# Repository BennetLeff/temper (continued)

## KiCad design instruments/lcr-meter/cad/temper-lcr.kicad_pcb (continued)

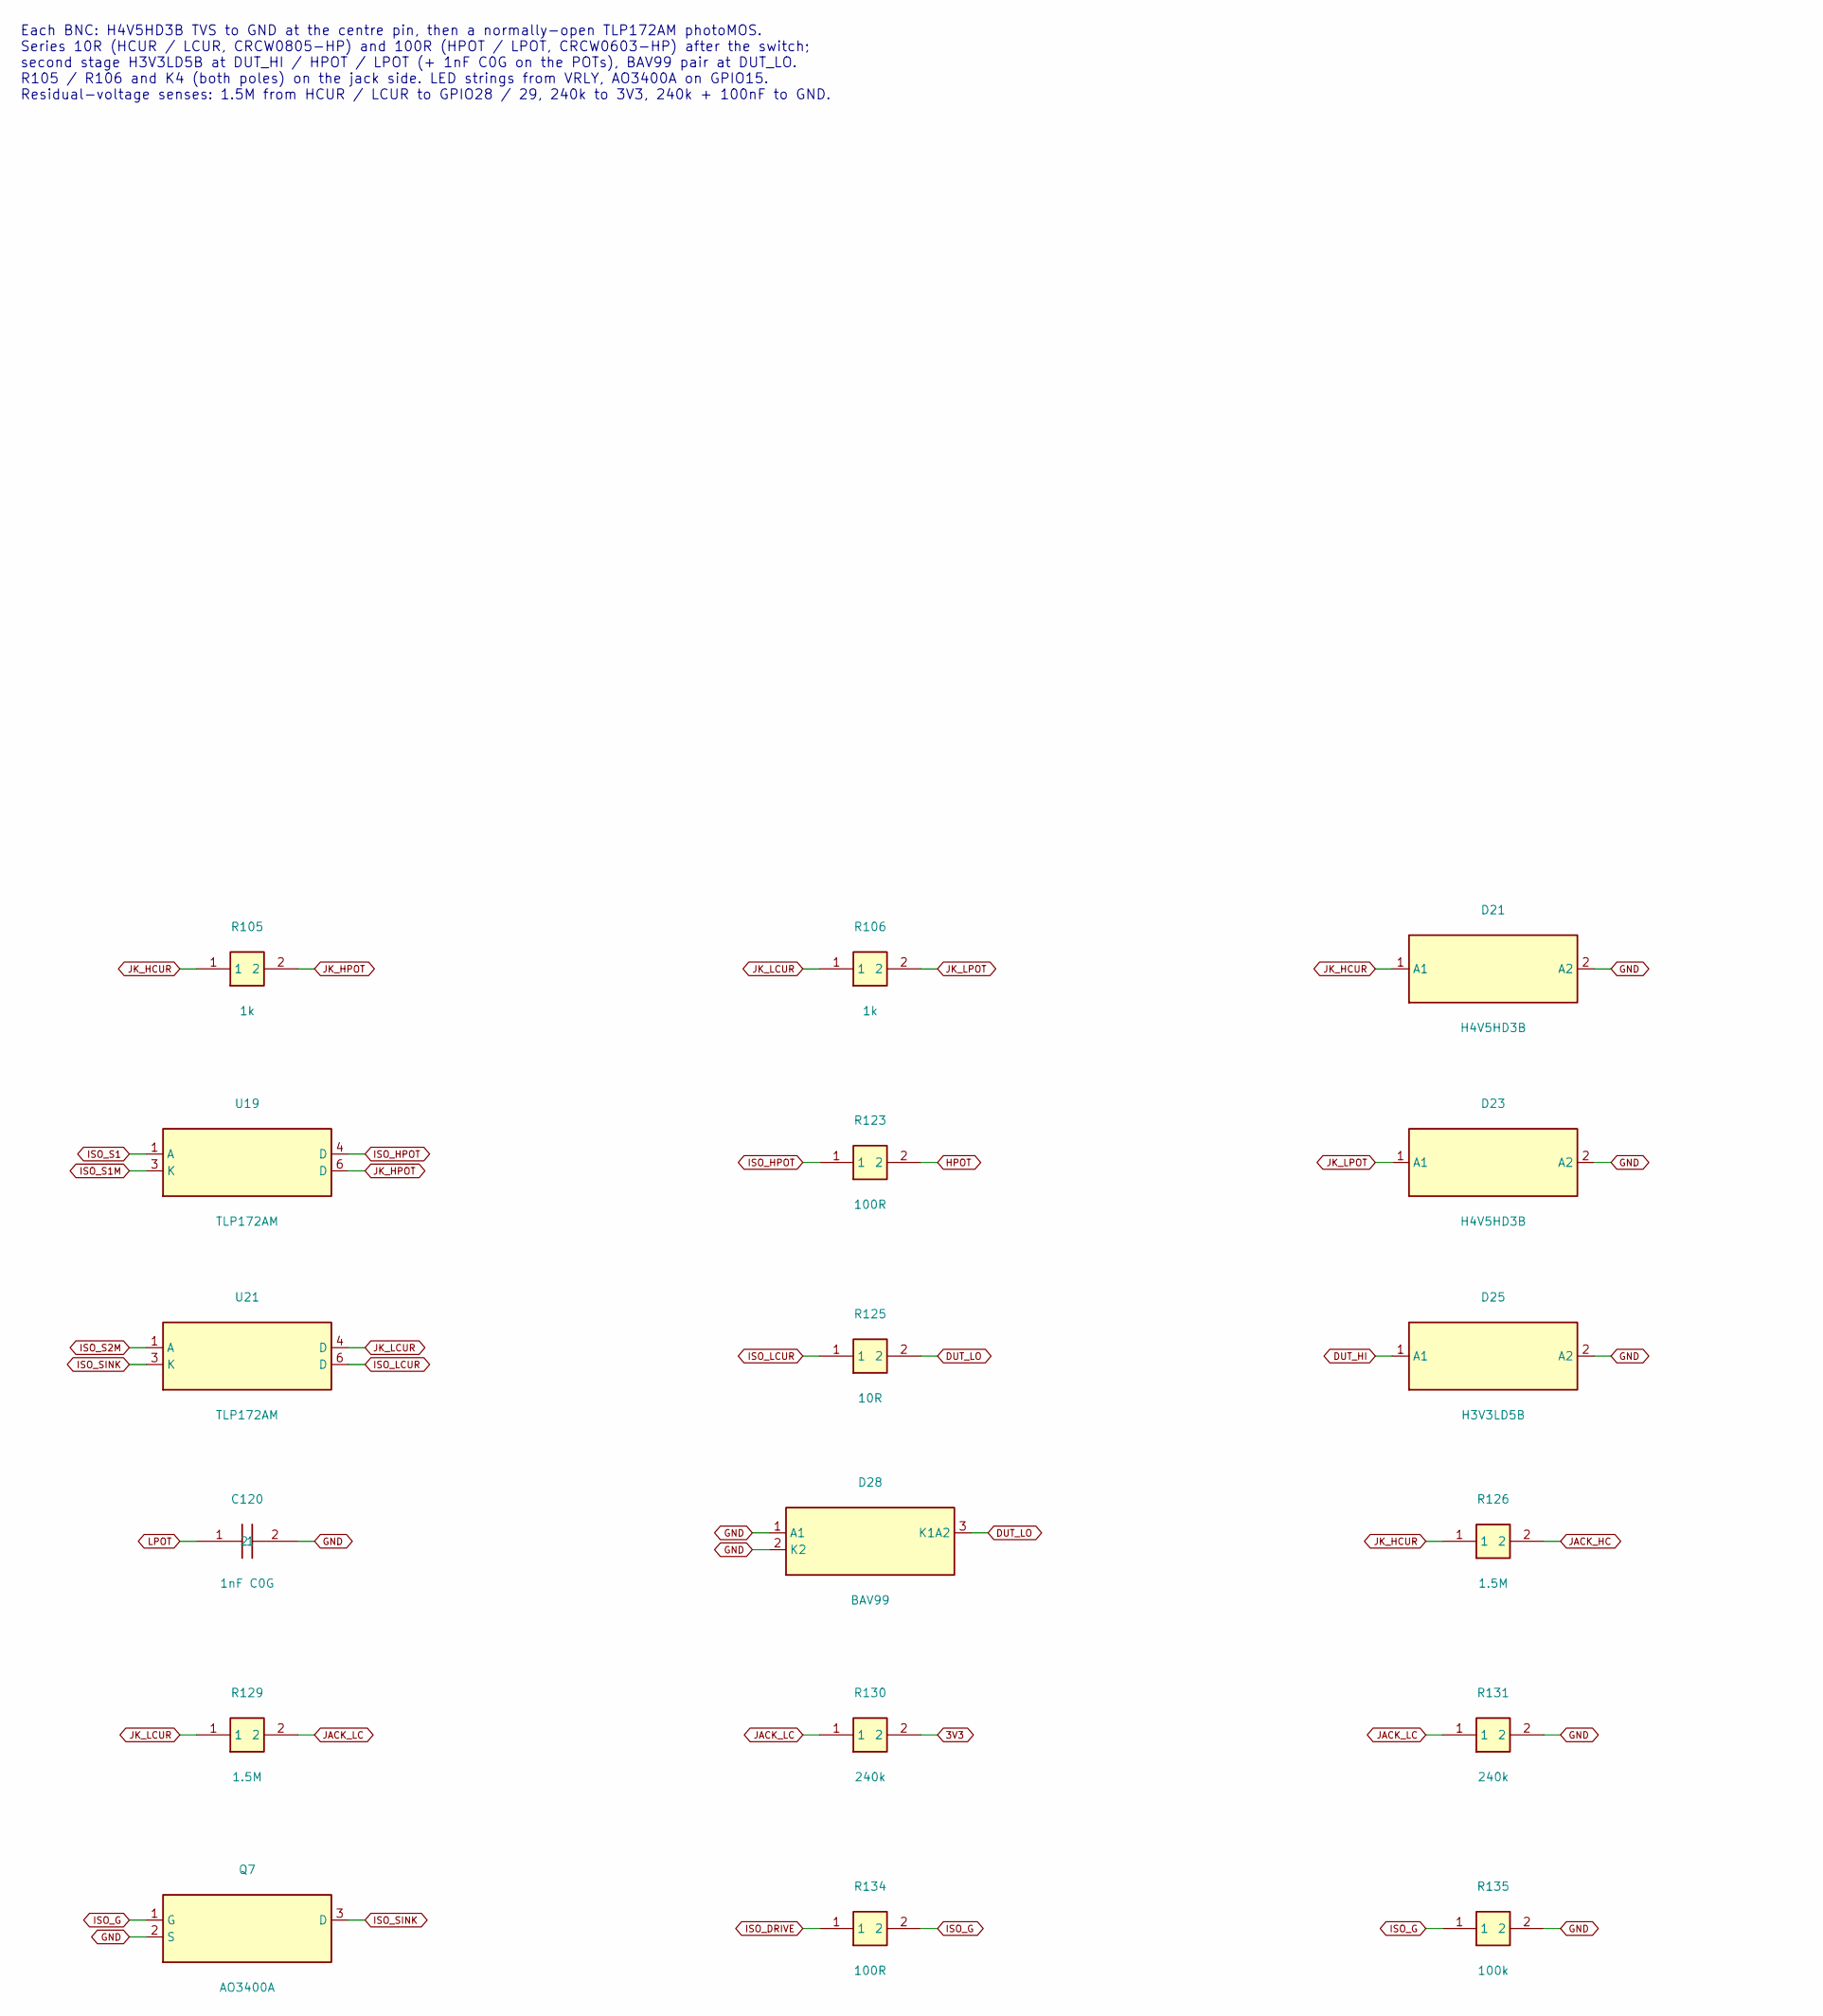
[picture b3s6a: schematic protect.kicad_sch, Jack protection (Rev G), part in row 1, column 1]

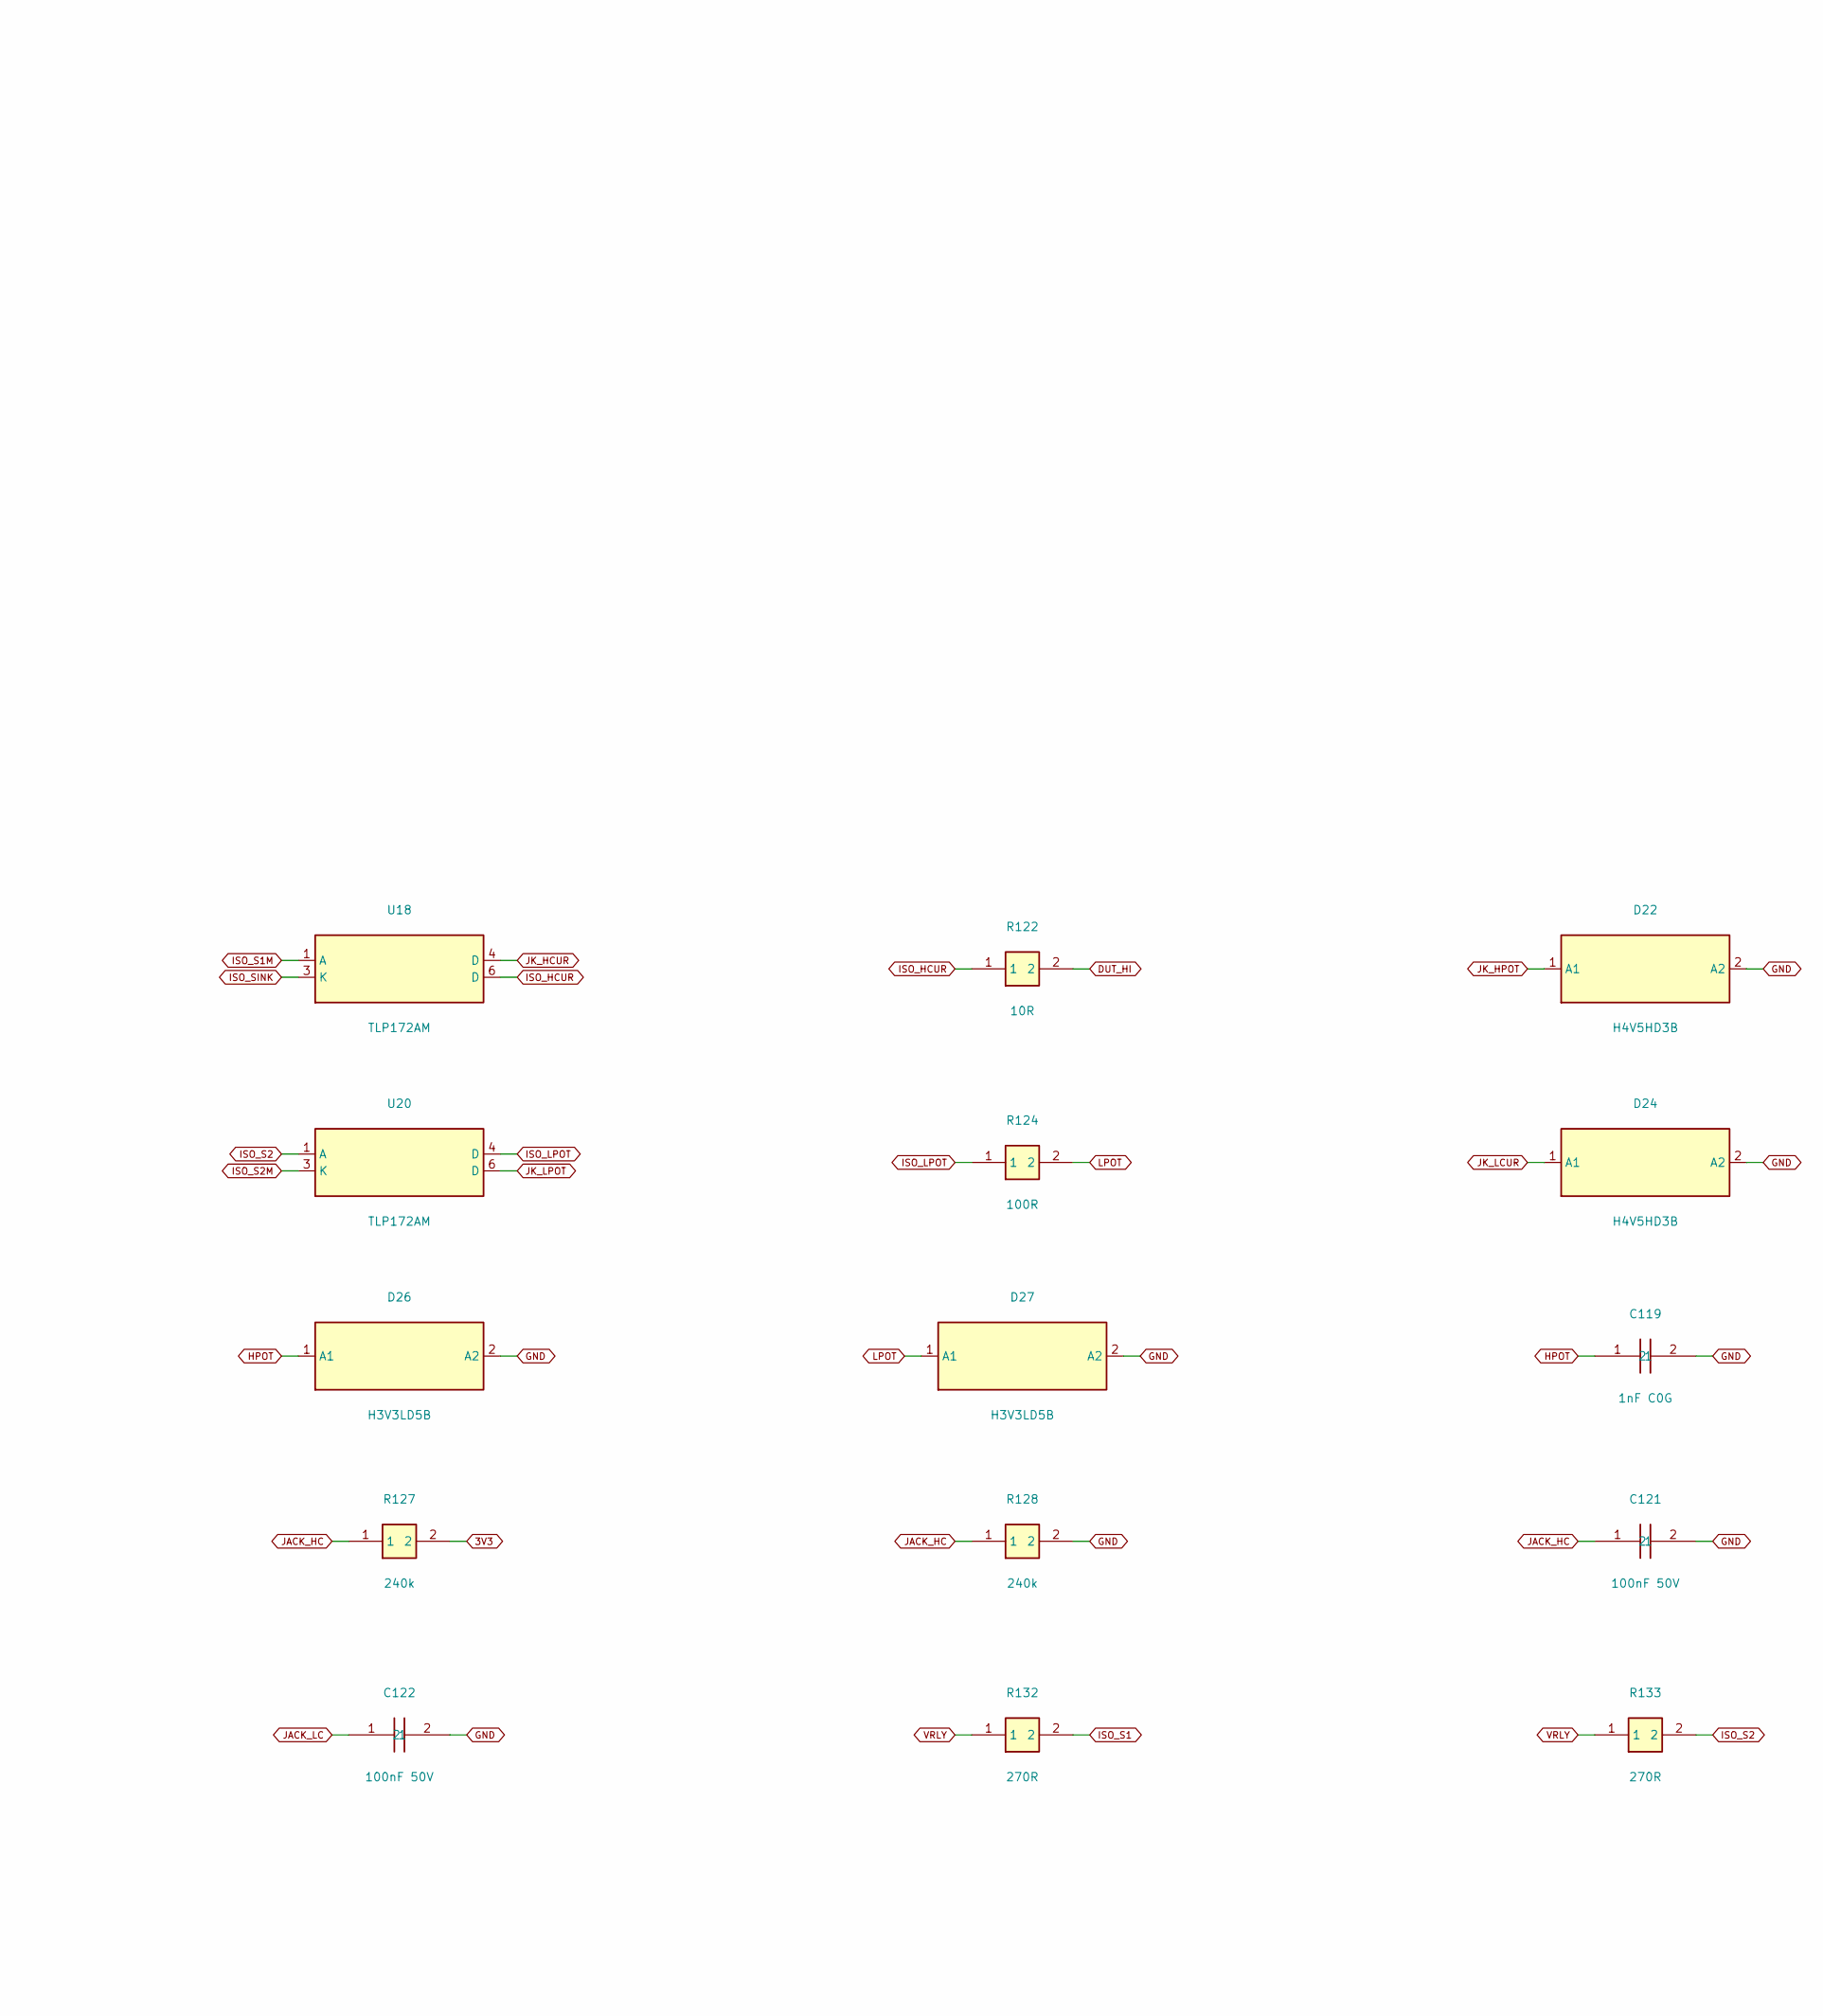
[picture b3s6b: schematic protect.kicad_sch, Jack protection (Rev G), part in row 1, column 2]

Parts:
C119, C120: 1nF C0G; C_0603_1608Metric; MPN CC0603JRNPO9BN102; LCSC C106246
C121, C122: 100nF 50V; C_0603_1608Metric; MPN CC0603KRX7R9BB104; LCSC C14663
D21, D22, D23, D24: H4V5HD3B; D_SOD-323_HJC; MPN H4V5HD3B; LCSC C20615803
D25, D26, D27: H3V3LD5B; D_SOD-523; MPN H3V3LD5B; LCSC C20615817
D28: BAV99; SOT-23; MPN BAV99,215; LCSC C2500
Q7: AO3400A; SOT-23; MPN AO3400A; LCSC C20917
R105, R106: 1k; R_0603_1608Metric; MPN 0603WAF1001T5E; LCSC C21190
R122, R125: 10R; R_0805_2012Metric; MPN CRCW080510R0FKEAHP; LCSC C844598
R123, R124: 100R; R_0603_1608Metric; MPN CRCW0603100RFKEAHP; LCSC C844725
R126, R129: 1.5M; R_0603_1608Metric; MPN 0603WAF1504T5E; LCSC C4172
R127, R128, R130, R131: 240k; R_0603_1608Metric; MPN 0603WAF2403T5E; LCSC C4197
R132, R133: 270R; R_0603_1608Metric; MPN 0603WAF2700T5E; LCSC C22966
R134: 100R; R_0603_1608Metric; MPN 0603WAF1000T5E; LCSC C22775
R135: 100k; R_0603_1608Metric; MPN 0603WAF1003T5E; LCSC C25803
U18, U19, U20, U21: TLP172AM; Toshiba_11-4M1S; MPN TLP172AM(TPL,E); LCSC C2152276

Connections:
3V3: R127.2, R130.2; also elsewhere on the board
DUT_HI: D25.1 (A1), R122.2; also elsewhere on the board
DUT_LO: D28.3 (K1A2), R125.2; also elsewhere on the board
GND: C119.2, C120.2, C121.2, C122.2, D21.2 (A2), D22.2 (A2), D23.2 (A2), D24.2 (A2), D25.2 (A2), D26.2 (A2), D27.2 (A2), D28.1 (A1), D28.2 (K2), Q7.2 (S), R128.2, R131.2, R135.2; also elsewhere on the board
HPOT: C119.1, D26.1 (A1), R123.2; also elsewhere on the board
ISO_DRIVE: R134.1; also elsewhere on the board
ISO_G: Q7.1 (G), R134.2, R135.1
ISO_HCUR: R122.1, U18.6 (D)
ISO_HPOT: R123.1, U19.4 (D)
ISO_LCUR: R125.1, U21.6 (D)
ISO_LPOT: R124.1, U20.4 (D)
ISO_S1: R132.2, U19.1 (A)
ISO_S1M: U18.1 (A), U19.3 (K)
ISO_S2: R133.2, U20.1 (A)
ISO_S2M: U20.3 (K), U21.1 (A)
ISO_SINK: Q7.3 (D), U18.3 (K), U21.3 (K)
JACK_HC: C121.1, R126.2, R127.1, R128.1; also elsewhere on the board
JACK_LC: C122.1, R129.2, R130.1, R131.1; also elsewhere on the board
JK_HCUR: D21.1 (A1), R105.1, R126.1, U18.4 (D); also elsewhere on the board
JK_HPOT: D22.1 (A1), R105.2, U19.6 (D); also elsewhere on the board
JK_LCUR: D24.1 (A1), R106.1, R129.1, U21.4 (D); also elsewhere on the board
JK_LPOT: D23.1 (A1), R106.2, U20.6 (D); also elsewhere on the board
LPOT: C120.1, D27.1 (A1), R124.2; also elsewhere on the board
VRLY: R132.1, R133.1; also elsewhere on the board

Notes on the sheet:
Each BNC: H4V5HD3B TVS to GND at the centre pin, then a normally-open TLP172AM photoMOS. Series 10R (HCUR / LCUR, CRCW0805-HP) and 100R (HPOT / LPOT, CRCW0603-HP) after the switch; second stage H3V3LD5B at DUT_HI / HPOT / LPOT (+ 1nF C0G on the POTs), BAV99 pair at DUT_LO. R105 / R106 and K4 (both 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
